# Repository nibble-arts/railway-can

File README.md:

# Railway-CAN
*Das Projekt ist in der Phase des Brainstormings.*

Ziel des Projekts ist es, eine analog betriebene Modelleisenbahn so auszurüsten, dass ein weitgehend vorbildlicher Betrieb erreicht wird. Weichen, Signale und Fahrstraßen bedient das Stellwerk, eine Lokomotive wird von einem Lokführer gesteuert, er sieht seine Signale und kann darauf reagieren.

Das System besteht aus den Anlagenmodulen, dem Stellpult, den Fahrpulten und der Zentrale.

Es handelt sich dann um eine digitale Modellbahn, bei der jedoch die Anlage digitalisiert wird und nicht die Fahrzeuge. Jede analoge (und auch digitaler) Lok kann darauf ohne Eingriff in das Fahrzeug eingesetzt werden.

Die befahrenen Gleisabschnitte werden automatisch vom System geschalten. Es können so viele Loks gleichzeitig fahren, wie es freie Gleisabschnitte gibt. Für jede Lok muss dann auch ein Fahrregler und Lokführer vorhanden sein.

Um nicht von propräitärer Software abhängig zu sein, soll die gesamte Steuerung mit den Hardware-Bausteinen und der Software von Railway-CAN abgedeckt sein. Ich greife dabei auf die Erfahrungen aus dem [Loco-CAN](https://github.com/loco-can) Projekt zurück, dass eine ähnliche Hardware verwendet.

Der Aufbau und die Verkabelung der Anlage, sowie die nötigen Einstellunge sollen für jeden Modellbahner auch ohne Programmierkenntnisse umsetzbar sein und gleichzeitig der Verkabelungsaufwand reduziert werden. Dies wird durch den Einsatz eines CAN-Busses erreicht.

Da das gesamte Projekt, Hard- wie Software, open source sind, können auch in Zukunft jederzeit Module für Erweiterungen nachgefertigt werden. 

## Anlage
Je nach existierender Verkabelung der Modellbahn können die Anlagemodule direkt auf der Anlage verlegt werden oder beim bisherigen Stellpult. Wichtig ist, dass Kabel die Schienen, die Weichen oder Signalen mit den Modulen verbinden müssen. Bei einer Neuverkabelung ist es ratsam die Module unter der Anlage anzubringen. Alle Module werden an eine Versorgung-Ringleitung angeschlossen, die von einem Netzteil für die gesamte Anlage gespeist wird. Es ist auch möglich bei großen Anlagen mehrere Netzteile für Anlagenteile zu verwenden, es muss dann nur der Minuspol aller Netzteile verbunden sein.

## Stellwerk
[Stellwerk](docs/signal_box.md)

Das Stellwerk ist ein physisch aufgebautes Spurplanstellwerk der Type Siemens SP Dr S60. Es beinhaltet alle Bedienelemente und Ausleuchtungen zum Stellen der Weichen, Signale, Schranken und Fahrstraßen.

Die Blöcke werden aus 3D-gedruckten Teilen zusammengesetzt. Im Inneren sitzt die Elektronik für den jeweiligen Block mit Tasten, LEDs oder einem Display für die Zugnummer.

Die Verkabelung der einzelnen Blöcke im Atelier untereinander ist ganz einfach, werden sie lediglich mit einem vierpoligen Kabel beliebig miteinander verbunden. Die letzte Verbindung läuft zur Zentrale.

Die Zuordnung zwischen den Anlagenmodulen und den Stellwerksblöcken muss nur einmalig erfolgen und ist ganz einfach gehalten.

Für eine große Anlage können auch mehrere kleine Stellwerke aufgebaut werden, die dann zusammenarbeiten.

## Anlagenmodule
[Abschnitts-Steuerung](docs/section_controller.md)

Auf der Anlage werden die isolierten Gleisabschnitte, die Signal, Weichen und Schrankenanlagen mit jeweils dem passenden Anlagenmodul verbunden. Für die verschiedenen Aufgaben gibt es unterschiedliche Module.

Jedes Anlagenmodul besitzt einen Anschluss für die DC-Versorgungsspannung und zwei Busstecker. Die Fahrspannung wird in jedem Modul gesteuert und darf 2 Ampere in dem Bereich nicht überschreiten. Bei einem Kurzschluss in einem Abschnitt schaltet nur dieses Modul ab, die restliche Anlage bleibt weiter in Betrieb.

Der CAN-Bus wird einfach von einem Modul zum nächsten mit zweipoligen Kabeln verbunden. Es können mindestens 100 Module an einem Bus betrieben werden, die Zentrale bietet mehrere Busse an. Die maximale Länge einer Busleitung sollte 100 Meter nicht überschreiten.

Je nach Modul gibt es noch die nötigen Anschlüsse zur Anlage (Gleis, Signal, Weichenantrieb, Gleisüberwachung).

### Gleismodul
Das Gleismodul ist für ein durchgehendes Gleis zwischen zwei Signalen gedacht. Es wird mit zwei Kabeln an den Gleisabschnitt angeschlossen. Jeder Abschnitt muss beidpolig von den benachbarten Gleisen isoliert sein. 

Signale, Kreuzungen und Weichen benötigen einen eigenen Abschnitt. Eisenbahnkreuzungen werden nur durch einen Freimelder überwacht.

### Signalmodul
Das Signalnodule wird mit zwei Kabeln an den Gleisabschnitt im Bereich des Signals angeschlossen. Zusätzlich gibt es Anschlüsse für die Ansteuerung eines Licht- oder Formsignals.

Für die Überwachung des Signals wird ein Gleisfreimelder verwendet.

### Weichenmodul
[Weichen](docs/switch.md)

### Eisenbahnkreuzungsmodul
Das Modul für Eisenbahnkreuzungen ist mit dem Signalmodul ident, die jeweilige Funktion wird über einen Schalter am Modul gewählt. 

Die Blinklichtanlage wird mit den Anschlüssen für das Signal verbunden. Es ist kein eigener Gleisabschnitt nötig.

## Gleisfreimeldung
[Freimeldesensor](docs/sensor.md)

Für einen vorbildlichen Betrieb ist es wichtig zu wissen, welcher Abschnitt von Fahrzeugen besetzt ist. Um nicht nur Lokomotiven und deren Stromverbrauch zu erkennen, sondern den gesamten Zug, werden Time of Flight-Sensoren (ToF) eingesetzt, die einen bestimmten Raum mittels Laserstrahl überwachen. Es wird so die Anwesenheit jeglichen Fahrzeuges erkannt, ohne jede Waggonachse mit einem Widerstand versehen zu müssen. Ein geschobenen Zug bleibt korrekt vor dem Signal stehen oder löst zum richtigen Zeitpunkt eine Zwangsbremsung beim Überfahrenen Signal aus.

Die Feimeldung wird über die ToF-Sensoren, der Strommessung am Gleis und dem Status der Gleis- und Signalnodule bestimmt.

## Zentrale
[Zentrale](docs/central.md)

Die Zentrale verdient den Namen eigentlich nicht, da sie keine zentrale Steuerung vereint, sondern lediglich die Kommunikation aller Komponenten untereinander ermöglicht. 

Sie besitzt einen USB-Anschluss zum Anschluss an einen PC. Ein Computer ist für den normalen Betrieb NICHT nötig. Es können jedoch alle Schalt- und Fahrbefehle von einem Computerprogramm gesendet werden, um so z.B. ein Fahrplan vorgeben zu können. Die Zugfahrten können in dem Fall manuell erfolgen oder auch automatisch.

Eine Software dafür ist derzeit nicht Teil des Projekts. Das Protokoll zur Steuerung wird jedoch hier offengelegt.

## Fahrpult
Jedes Fahrpult kann mir einer Lok verbunden werden, indem sie Loknummer eingegeben wird. Das Gleis, auf dem die Lok steht, erhält die gleiche Nummer und wird mit diesen Fahrpult gesteuert.

Es können mehrere Fahrpulte angeschlossen werden. Die Fahrpulte bieten einen Fahrregler, einen Schalter für die Fahrtrichtung und ein Display, auf dem die nächsten Signale angezeigt werden. Über einen Drehregler lässt sich die Loknummer einstellen.

## Betriebszustand speichern
[Persistance](docs/persistance.md)

Wird das System ausgeschaltet, speichert die Zentrale automatisch den letzten Betriebszustand. Nach dem Einschalten wird dieser Zustand wieder geladen. Hat sich die Zugaufstellung nicht verändert, kann der Betrieb gleich wieder aufgenommen werden.

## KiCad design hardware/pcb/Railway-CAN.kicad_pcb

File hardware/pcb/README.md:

# PCBs
Die Schaltungen und Platinen werden mit KiCAD entwickelt und stehen hier zur Verfügung.

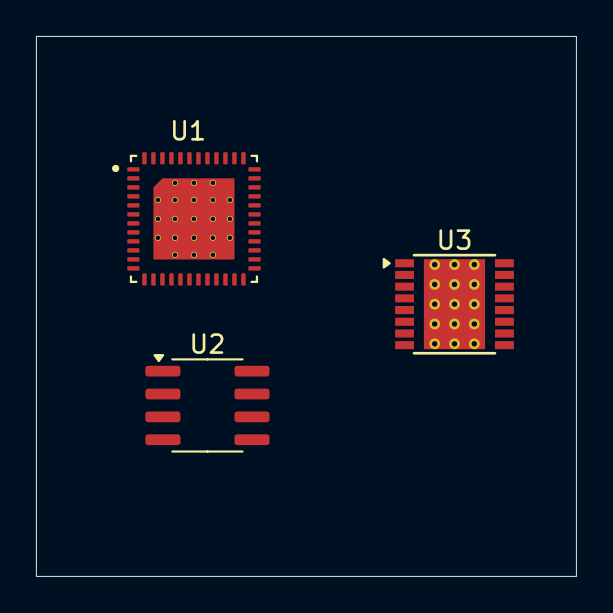
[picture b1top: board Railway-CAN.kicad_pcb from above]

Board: 2 copper layers, 30.0 x 30.0 mm, 3 parts (0 on the bottom side), 2 nets, no tracks yet.

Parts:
U1: ESP32-PICO-V3-02
U2: MCP2551-I-SN; SOIC-8_3.9x4.9mm_P1.27mm
U3: DRV8801PWP; HTSSOP-16-1EP_4.4x5mm_P0.65mm_EP3.4x5mm_Mask3x3mm_ThermalVi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

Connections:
unnamed: U1.3 (VDDA3P3), U1.4 (VDDA3P3)
unnamed: U1.1 (VDDA), U1.43 (VDDA), U1.46 (VDDA)

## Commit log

2024-10-28 Rename RCAN SPDrS60 3d printing.jpg to images/RCAN_SPDrS60_3d_printing.jpg
2024-10-28 Rename hardware/ESP32-PICO-V3-02.kicad_sym to hardware/libraries/ESP32-PICI/ESP32-PICO-V3-02.kicad_sym
2024-10-28 Rename ESP32-PICO-V3-02.kicad_sym to ESP32-PICO-V3-02.kicad_sym
2024-10-28 Rename hardware/XCVR_ESP32-PICO-V3-02.kicad_mod to hardware/libraries/ESP32-PICO/XCVR_ESP32-PICO-V3-02.kicad_mod
2024-10-28 Rename hardware/libraries/ESP32-PICO/README.md to hardware/libraries/README.md
2024-10-30 Create persistance md
2024-10-30 Rename persistance md to persistance.md
